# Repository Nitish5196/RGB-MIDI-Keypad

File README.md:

# RGB MIDI Keypad 
A 25 key capacitive touch MIDI keypad PCB with :
- Seeed Studio XIAO RP2040 : To process everything 
- MPR121 capacitive touch sensors : to connect the 25 keys (the rp2040 doest not have enough gpio pins for 25 keys so this is needed)
- capacitive keys - no physical keys , just touch the copper pads to make music
- RGB LEDs - LED under each key which lights up when you touch a copper pad
- Octave Control Switch - Click the 2 mechanical keys to switch between up and down octaves
- Rotary Encoder - to control the volume and much more (tbh its there cause its fun to twist this and act like a DJ)
- Slide Potentiometers - to control filters , effects and anything u want
- A display - to display the settings and cool animations
- A power ON LED and a LED which blinks with you press any key except the copper pads
### HERE IS THE IMAGE OF THE PCB 

## BOM:
| Components | Qty | Unit Price | Total Price | Link |
| -------- | -------- | -------- |  -------- | -------- | 
| Seeed Studio XIAO RP2040 | 1 | $5.59 | $5.59 | [supplier](https://robu.in/product/seeed-studio-xiao-rp2040-v1-0/) | 
| MPR121 Capacitive Touch Modules | 3 | $1.15 | $3.45 | [supplier](https://robu.in/product/mpr121-breakout-v12-capacitive-touch-sensor-controller-module-i2c-keyboard/)
| 0.91 inch 128x32 Blue OLED Display | 1 | $2.23 | $2.23 | [supplier](https://robu.in/product/0-91-inch-128x32-i2c-iic-serial-blue-oled-lcd-display-module/)
| Rotary encoder Dev board | 1 | $1.04 | $1.04| [link](https://robu.in/product/EC11%20Rotary%20Encoder%20Module%20with%20Knob%20Cap%20for%20Development%20Boards/) |
| WS2812B LED | 25 | $0.08 | $2.00 | [link](https://robu.in/product/sme-ws2812b-2020-addressable-rgb-pixel-led-worldsemi/) |
| Power Indicator LED | 2 | $0.011  | $0.8 | [link](https://robu.in/product/3mm-green-dip-led-pack-of-50/) | 
| PTA2043 Slide Potentiometer | 2 | $2.61 | $5.27 | [link](https://robu.in/product/pta2043-2010cib254-bourns/) | 
| SW_Cherry_MX switch | 2 | $0.5 | $1 | [link](https://www.sunrom.com/p/cherry-mx-blue-switch-mx1a-e1nn) | 
| PCB | 1 | $10 | $10 | [link](https://robu.in/product/online-pcb-manufacturing-service/) |
| Total:||$30 |

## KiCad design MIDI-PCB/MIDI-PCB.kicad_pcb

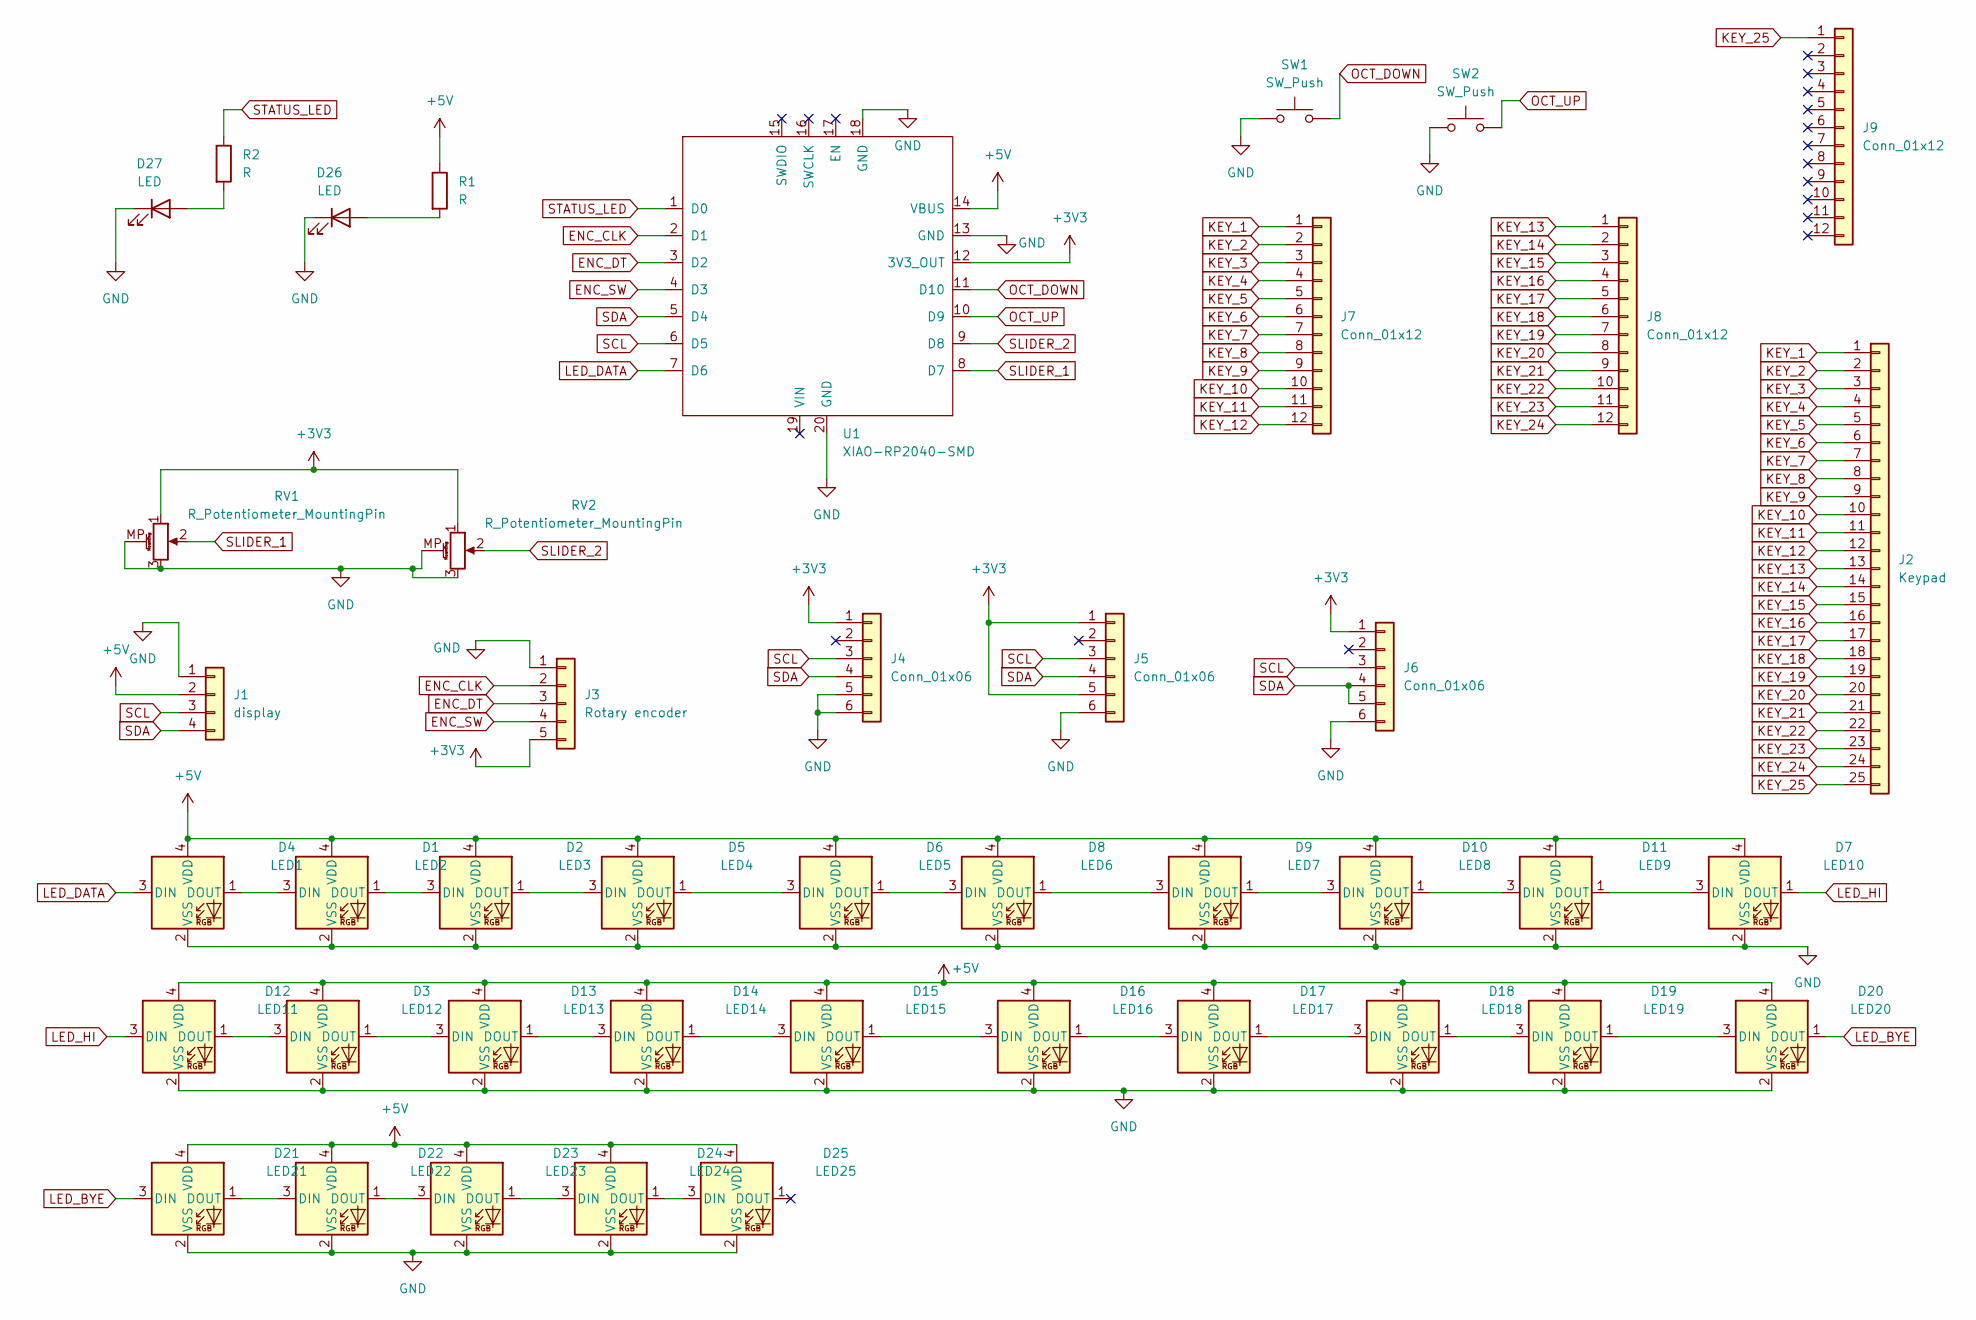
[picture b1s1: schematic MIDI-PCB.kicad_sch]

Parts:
D1: LED2; LED_WS2812B-2020_PLCC4_2.0x2.0mm
D2: LED3; LED_WS2812B-2020_PLCC4_2.0x2.0mm
D3: LED12; LED_WS2812B-2020_PLCC4_2.0x2.0mm
D4: LED1; LED_WS2812B-2020_PLCC4_2.0x2.0mm
D5: LED4; LED_WS2812B-2020_PLCC4_2.0x2.0mm
D6: LED5; LED_WS2812B-2020_PLCC4_2.0x2.0mm
D7: LED10; LED_WS2812B-2020_PLCC4_2.0x2.0mm
D8: LED6; LED_WS2812B-2020_PLCC4_2.0x2.0mm
D9: LED7; LED_WS2812B-2020_PLCC4_2.0x2.0mm
D10: LED8; LED_WS2812B-2020_PLCC4_2.0x2.0mm
D11: LED9; LED_WS2812B-2020_PLCC4_2.0x2.0mm
D12: LED11; LED_WS2812B-2020_PLCC4_2.0x2.0mm
D13: LED13; LED_WS2812B-2020_PLCC4_2.0x2.0mm
D14: LED14; LED_WS2812B-2020_PLCC4_2.0x2.0mm
D15: LED15; LED_WS2812B-2020_PLCC4_2.0x2.0mm
D16: LED16; LED_WS2812B-2020_PLCC4_2.0x2.0mm
D17: LED17; LED_WS2812B-2020_PLCC4_2.0x2.0mm
D18: LED18; LED_WS2812B-2020_PLCC4_2.0x2.0mm
D19: LED19; LED_WS2812B-2020_PLCC4_2.0x2.0mm
D20: LED20; LED_WS2812B-2020_PLCC4_2.0x2.0mm
D21: LED21; LED_WS2812B-2020_PLCC4_2.0x2.0mm
D22: LED22; LED_WS2812B-2020_PLCC4_2.0x2.0mm
D23: LED23; LED_WS2812B-2020_PLCC4_2.0x2.0mm
D24: LED24; LED_WS2812B-2020_PLCC4_2.0x2.0mm
D25: LED25; LED_WS2812B-2020_PLCC4_2.0x2.0mm
D26, D27: LED; LED_D3.0mm
J1: display; PinHeader_1x04_P2.54mm_Vertical
J2: Keypad; KEYPAD
J3: Rotary encoder; PinHeader_1x05_P2.54mm_Vertical
J4, J5, J6: Conn_01x06; PinHeader_1x06_P2.54mm_Vertical
J7, J8, J9: Conn_01x12; PinHeader_1x12_P2.54mm_Vertical
R1, R2: R; R_0805_2012Metric
RV1, RV2: R_Potentiometer_MountingPin; Potentiometer_Bourns_PTA2043_Single_Slide
SW1, SW2: SW_Push; SW_Cherry_MX_1.00u_PCB
U1: XIAO-RP2040-SMD

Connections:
+3V3: J3.5, J4.1, J5.1, J5.5, J6.1, RV1.1, RV2.1, U1.12 (3V3_OUT)
+5V: D1.4 (VDD), D2.4 (VDD), D3.4 (VDD), D4.4 (VDD), D5.4 (VDD), D6.4 (VDD), D7.4 (VDD), D8.4 (VDD), D9.4 (VDD), D10.4 (VDD), D11.4 (VDD), D12.4 (VDD), D13.4 (VDD), D14.4 (VDD), D15.4 (VDD), D16.4 (VDD), D17.4 (VDD), D18.4 (VDD), D19.4 (VDD), D20.4 (VDD), D21.4 (VDD), D22.4 (VDD), D23.4 (VDD), D24.4 (VDD), D25.4 (VDD), J1.2, R1.1, U1.14 (VBUS)
ENC_CLK: J3.2, U1.2 (D1)
ENC_DT: J3.3, U1.3 (D2)
ENC_SW: J3.4, U1.4 (D3)
GND: D1.2 (VSS), D2.2 (VSS), D3.2 (VSS), D4.2 (VSS), D5.2 (VSS), D6.2 (VSS), D7.2 (VSS), D8.2 (VSS), D9.2 (VSS), D10.2 (VSS), D11.2 (VSS), D12.2 (VSS), D13.2 (VSS), D14.2 (VSS), D15.2 (VSS), D16.2 (VSS), D17.2 (VSS), D18.2 (VSS), D19.2 (VSS), D20.2 (VSS), D21.2 (VSS), D22.2 (VSS), D23.2 (VSS), D24.2 (VSS), D25.2 (VSS), D26.1 (K), D27.1 (K), J1.1, J3.1, J4.5, J4.6, J5.6, J6.6, RV1.3, RV1.MP (MountPin), RV2.3, RV2.MP (MountPin), SW1.1, SW2.1, U1.13 (GND), U1.18 (GND), U1.20 (GND)
KEY_1: J2.1, J7.1
KEY_2: J2.2, J7.2
KEY_3: J2.3, J7.3
KEY_4: J2.4, J7.4
KEY_5: J2.5, J7.5
KEY_6: J2.6, J7.6
KEY_7: J2.7, J7.7
KEY_8: J2.8, J7.8
KEY_9: J2.9, J7.9
KEY_10: J2.10, J7.10
KEY_11: J2.11, J7.11
KEY_12: J2.12, J7.12
KEY_13: J2.13, J8.1
KEY_14: J2.14, J8.2
KEY_15: J2.15, J8.3
KEY_16: J2.16, J8.4
KEY_17: J2.17, J8.5
KEY_18: J2.18, J8.6
KEY_19: J2.19, J8.7
KEY_20: J2.20, J8.8
KEY_21: J2.21, J8.9
KEY_22: J2.22, J8.10
KEY_23: J2.23, J8.11
KEY_24: J2.24, J8.12
KEY_25: J2.25, J9.1 (Pin_1_1)
LED_BYE: D20.1 (DOUT), D21.3 (DIN)
LED_DATA: D4.3 (DIN), U1.7 (D6)
LED_HI: D7.1 (DOUT), D12.3 (DIN)
unnamed: D1.3 (DIN), D4.1 (DOUT)
unnamed: D1.1 (DOUT), D2.3 (DIN)
unnamed: D2.1 (DOUT), D5.3 (DIN)
unnamed: D5.1 (DOUT), D6.3 (DIN)
unnamed: D6.1 (DOUT), D8.3 (DIN)
unnamed: D8.1 (DOUT), D9.3 (DIN)
unnamed: D9.1 (DOUT), D10.3 (DIN)
unnamed: D10.1 (DOUT), D11.3 (DIN)
unnamed: D7.3 (DIN), D11.1 (DOUT)
unnamed: D3.3 (DIN), D12.1 (DOUT)
unnamed: D3.1 (DOUT), D13.3 (DIN)
unnamed: D13.1 (DOUT), D14.3 (DIN)
unnamed: D14.1 (DOUT), D15.3 (DIN)
unnamed: D15.1 (DOUT), D16.3 (DIN)
unnamed: D16.1 (DOUT), D17.3 (DIN)
unnamed: D17.1 (DOUT), D18.3 (DIN)
unnamed: D18.1 (DOUT), D19.3 (DIN)
unnamed: D19.1 (DOUT), D20.3 (DIN)
unnamed: D21.1 (DOUT), D22.3 (DIN)
unnamed: D22.1 (DOUT), D23.3 (DIN)
unnamed: D23.1 (DOUT), D24.3 (DIN)
unnamed: D24.1 (DOUT), D25.3 (DIN)
unnamed: D26.2 (A), R1.2
unnamed: D27.2 (A), R2.2
OCT_DOWN: SW1.2, U1.11 (D10)
OCT_UP: SW2.2, U1.10 (D9)
SCL: J1.3, J4.3, J5.3, J6.3, U1.6 (D5)
SDA: J1.4, J4.4, J5.4, J6.4, J6.5, U1.5 (D4)
SLIDER_1: RV1.2, U1.8 (D7)
SLIDER_2: RV2.2, U1.9 (D8)
STATUS_LED: R2.1, U1.1 (D0)

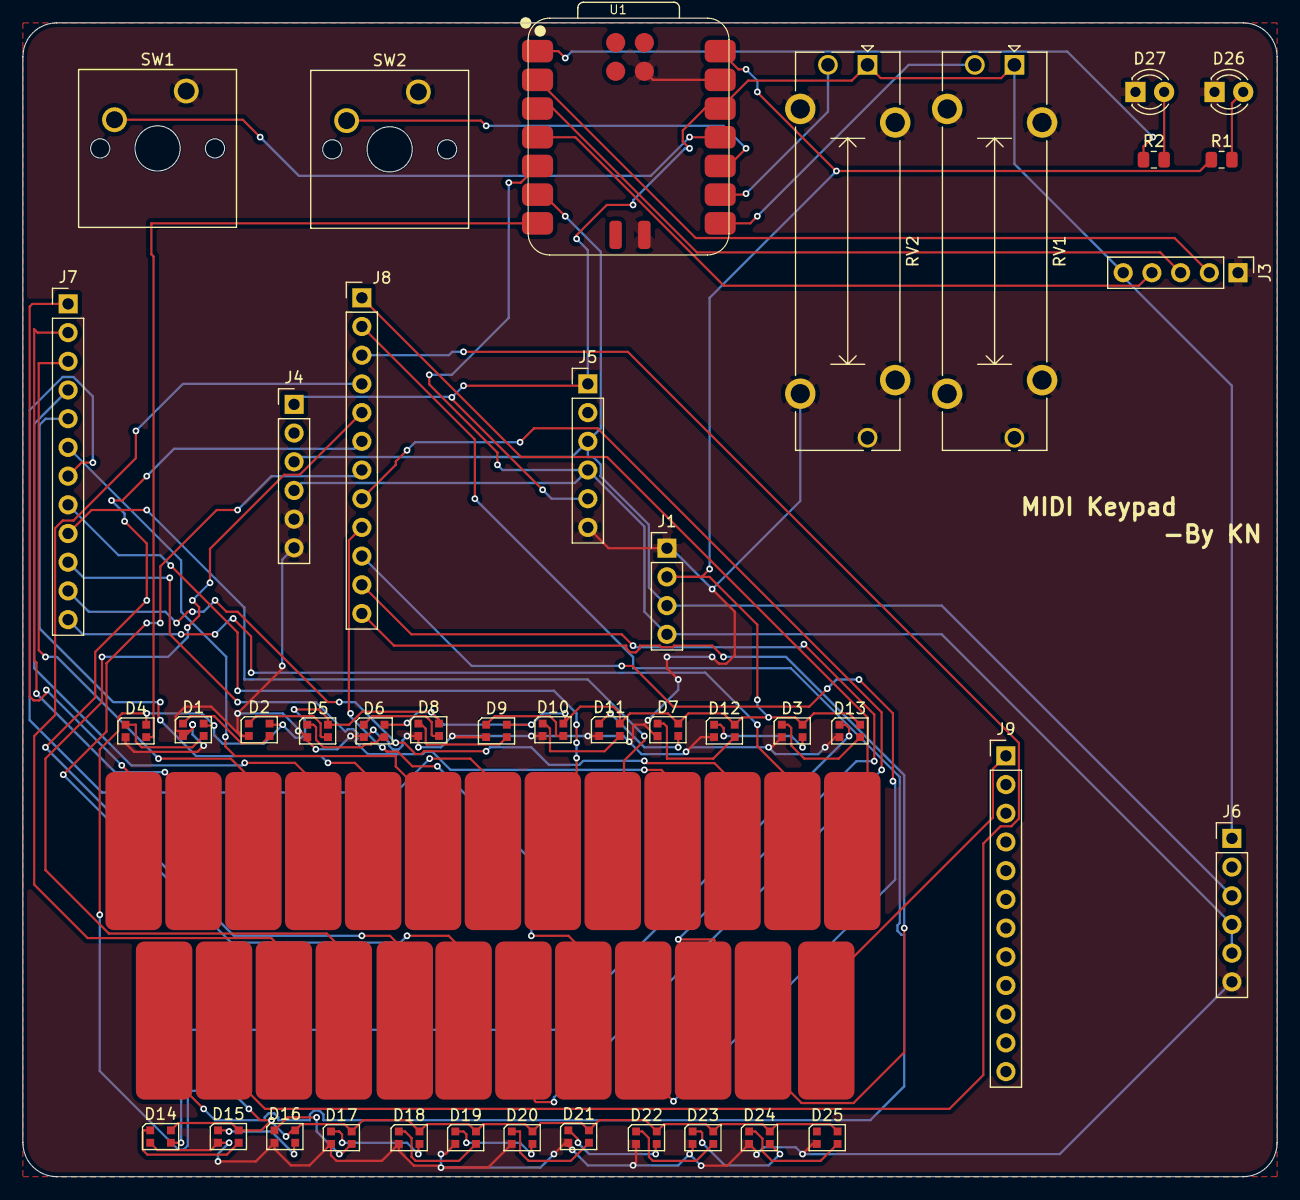
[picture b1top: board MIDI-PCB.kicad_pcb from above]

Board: 2 copper layers, 111.0 x 102.1 mm, 43 parts (0 on the bottom side), 65 nets.

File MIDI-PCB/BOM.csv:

"Id";"Designator";"Footprint";"Quantity";"Designation";"Supplier and ref";
1;"D1";"LED_WS2812B-2020_PLCC4_2.0x2.0mm";1;"LED2";;;
2;"D2";"LED_WS2812B-2020_PLCC4_2.0x2.0mm";1;"LED3";;;
3;"D3";"LED_WS2812B-2020_PLCC4_2.0x2.0mm";1;"LED12";;;
4;"D4";"LED_WS2812B-2020_PLCC4_2.0x2.0mm";1;"LED1";;;
5;"D5";"LED_WS2812B-2020_PLCC4_2.0x2.0mm";1;"LED4";;;
6;"D6";"LED_WS2812B-2020_PLCC4_2.0x2.0mm";1;"LED5";;;
7;"D7";"LED_WS2812B-2020_PLCC4_2.0x2.0mm";1;"LED10";;;
8;"D8";"LED_WS2812B-2020_PLCC4_2.0x2.0mm";1;"LED6";;;
9;"D9";"LED_WS2812B-2020_PLCC4_2.0x2.0mm";1;"LED7";;;
10;"D10";"LED_WS2812B-2020_PLCC4_2.0x2.0mm";1;"LED8";;;
11;"D11";"LED_WS2812B-2020_PLCC4_2.0x2.0mm";1;"LED9";;;
12;"D12";"LED_WS2812B-2020_PLCC4_2.0x2.0mm";1;"LED11";;;
13;"D13";"LED_WS2812B-2020_PLCC4_2.0x2.0mm";1;"LED13";;;
14;"D14";"LED_WS2812B-2020_PLCC4_2.0x2.0mm";1;"LED14";;;
15;"D15";"LED_WS2812B-2020_PLCC4_2.0x2.0mm";1;"LED15";;;
16;"D16";"LED_WS2812B-2020_PLCC4_2.0x2.0mm";1;"LED16";;;
17;"D17";"LED_WS2812B-2020_PLCC4_2.0x2.0mm";1;"LED17";;;
18;"D18";"LED_WS2812B-2020_PLCC4_2.0x2.0mm";1;"LED18";;;
19;"D19";"LED_WS2812B-2020_PLCC4_2.0x2.0mm";1;"LED19";;;
20;"D20";"LED_WS2812B-2020_PLCC4_2.0x2.0mm";1;"LED20";;;
21;"D21";"LED_WS2812B-2020_PLCC4_2.0x2.0mm";1;"LED21";;;
22;"D22";"LED_WS2812B-2020_PLCC4_2.0x2.0mm";1;"LED22";;;
23;"D23";"LED_WS2812B-2020_PLCC4_2.0x2.0mm";1;"LED23";;;
24;"D24";"LED_WS2812B-2020_PLCC4_2.0x2.0mm";1;"LED24";;;
25;"D25";"LED_WS2812B-2020_PLCC4_2.0x2.0mm";1;"LED25";;;
26;"D26, D27";"LED_D3.0mm";2;"LED";;;
27;"J1";"PinHeader_1x04_P2.54mm_Vertical";1;"display";;;
28;"J2";"KEYPAD";1;"Keypad";;;
29;"J3";"PinHeader_1x05_P2.54mm_Vertical";1;"Rotary encoder";;;
30;"J4, J5, J6";"PinHeader_1x06_P2.54mm_Vertical";3;"Conn_01x06";;;
31;"J7, J8, J9";"PinHeader_1x12_P2.54mm_Vertical";3;"Conn_01x12";;;
32;"R1, R2";"R_0805_2012Metric";2;"R";;;
33;"RV1, RV2";"Potentiometer_Bourns_PTA2043_Single_Slide";2;"R_Potentiometer_MountingPin";;;
34;"SW1, SW2";"SW_Cherry_MX_1.00u_PCB";2;"SW_Push";;;
35;"U1";"XIAO-RP2040-SMD";1;"XIAO-RP2040-SMD";;;
